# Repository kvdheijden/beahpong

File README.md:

# Beahpong
Linux (raspberry pi 4B+) kernel module + device tree for a Beahpong table

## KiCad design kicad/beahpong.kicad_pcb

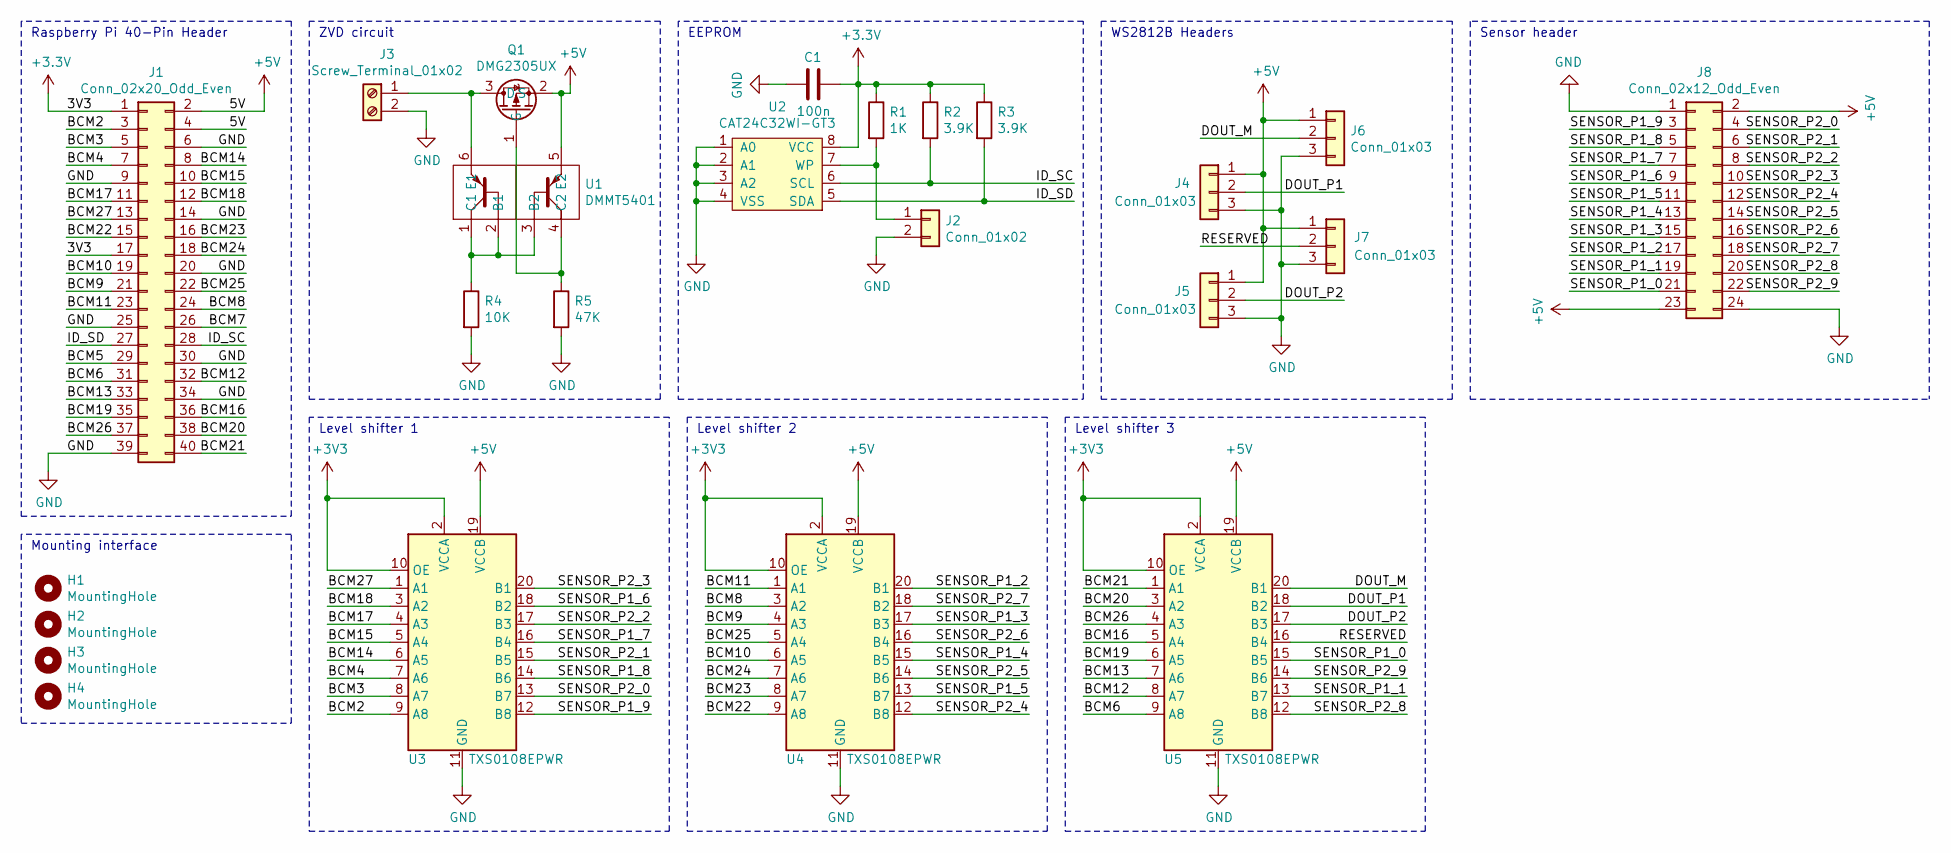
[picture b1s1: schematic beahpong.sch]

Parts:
C1: 100n; C_0402_1005Metric; LCSC C1525
H1, H2, H3, H4: MountingHole; MountingHole_2.75mm_M2.5_Land_6.2mm
J1: Conn_02x20_Odd_Even; PinSocket_2x20_P2.54mm_Vertical
J2: Conn_01x02; PinHeader_1x02_P2.54mm_Vertical
J3: Screw_Terminal_01x02; PhoenixContact_MC_1,5_2-G-3.5_1x02_P3.50mm_Horizontal
J4, J5, J6, J7: Conn_01x03; PinHeader_1x03_P2.54mm_Vertical
J8: Conn_02x12_Odd_Even; PinHeader_2x12_P2.54mm_Vertical
Q1: DMG2305UX; SOT-23; LCSC C144153
R1: 1K; R_0402_1005Metric; LCSC C11702
R2, R3: 3.9K; R_0402_1005Metric; LCSC C51721
R4: 10K; R_0402_1005Metric; LCSC C25744
R5: 47K; R_0402_1005Metric; LCSC C25792
U1: DMMT5401; SOT-23-6; LCSC C154733
U2: CAT24C32WI−GT3; SOIC-8_3.9x4.9mm_P1.27mm; LCSC C81193
U3, U4, U5: TXS0108EPWR; TSSOP-20_4.4x6.5mm_P0.65mm; LCSC C17206

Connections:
+5V: J1.2, J1.4, J4.1, J5.1, J6.1, J7.1, J8.2, J8.23, Q1.2 (S), U1.5 (E2), U3.19 (VCCB), U4.19 (VCCB), U5.19 (VCCB)
/BCM2: J1.3, U3.9 (A8)
/BCM3: J1.5, U3.8 (A7)
/BCM4: J1.7, U3.7 (A6)
/BCM6: J1.31, U5.9 (A8)
/BCM8: J1.24, U4.3 (A2)
/BCM9: J1.21, U4.4 (A3)
/BCM10: J1.19, U4.6 (A5)
/BCM11: J1.23, U4.1 (A1)
/BCM12: J1.32, U5.8 (A7)
/BCM13: J1.33, U5.7 (A6)
/BCM14: J1.8, U3.6 (A5)
/BCM15: J1.10, U3.5 (A4)
/BCM16: J1.36, U5.5 (A4)
/BCM17: J1.11, U3.4 (A3)
/BCM18: J1.12, U3.3 (A2)
/BCM19: J1.35, U5.6 (A5)
/BCM20: J1.38, U5.3 (A2)
/BCM21: J1.40, U5.1 (A1)
/BCM22: J1.15, U4.9 (A8)
/BCM23: J1.16, U4.8 (A7)
/BCM24: J1.18, U4.7 (A6)
/BCM25: J1.22, U4.5 (A4)
/BCM26: J1.37, U5.4 (A3)
/BCM27: J1.13, U3.1 (A1)
/DOUT_M: J6.2, U5.20 (B1)
/DOUT_P1: J4.2, U5.18 (B2)
/DOUT_P2: J5.2, U5.17 (B3)
/ID_SC: J1.28, R2.2, U2.6 (SCL)
/ID_SD: J1.27, R3.2, U2.5 (SDA)
/RESERVED: J7.2, U5.16 (B4)
/SENSOR_P1_0: J8.21, U5.15 (B5)
/SENSOR_P1_1: J8.19, U5.13 (B7)
/SENSOR_P1_2: J8.17, U4.20 (B1)
/SENSOR_P1_3: J8.15, U4.17 (B3)
/SENSOR_P1_4: J8.13, U4.15 (B5)
/SENSOR_P1_5: J8.11, U4.13 (B7)
/SENSOR_P1_6: J8.9, U3.18 (B2)
/SENSOR_P1_7: J8.7, U3.16 (B4)
/SENSOR_P1_8: J8.5, U3.14 (B6)
/SENSOR_P1_9: J8.3, U3.12 (B8)
/SENSOR_P2_0: J8.4, U3.13 (B7)
/SENSOR_P2_1: J8.6, U3.15 (B5)
/SENSOR_P2_2: J8.8, U3.17 (B3)
/SENSOR_P2_3: J8.10, U3.20 (B1)
/SENSOR_P2_4: J8.12, U4.12 (B8)
/SENSOR_P2_5: J8.14, U4.14 (B6)
/SENSOR_P2_6: J8.16, U4.16 (B4)
/SENSOR_P2_7: J8.18, U4.18 (B2)
/SENSOR_P2_8: J8.20, U5.12 (B8)
/SENSOR_P2_9: J8.22, U5.14 (B6)
GND: C1.1, J1.6, J1.9, J1.14, J1.20, J1.25, J1.30, J1.34, J1.39, J2.2, J3.2, J4.3, J5.3, J6.3, J7.3, J8.1, J8.24, R4.2, R5.2, U2.1 (A0), U2.2 (A1), U2.3 (A2), U2.4 (VSS), U3.11 (GND), U4.11 (GND), U5.11 (GND)
unnamed: J2.1, R1.2, U2.7 (WP)
unnamed: J3.1, Q1.3 (D), U1.6 (E1)
unnamed: Q1.1 (G), R5.1, U1.4 (C2)
unnamed: R4.1, U1.1 (C1), U1.2 (B1), U1.3 (B2)

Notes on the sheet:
Raspberry Pi 40-Pin Header
ZVD circuit
EEPROM
Mounting interface
Level shifter 2
Level shifter 1
Level shifter 3
WS2812B Headers
Sensor header

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
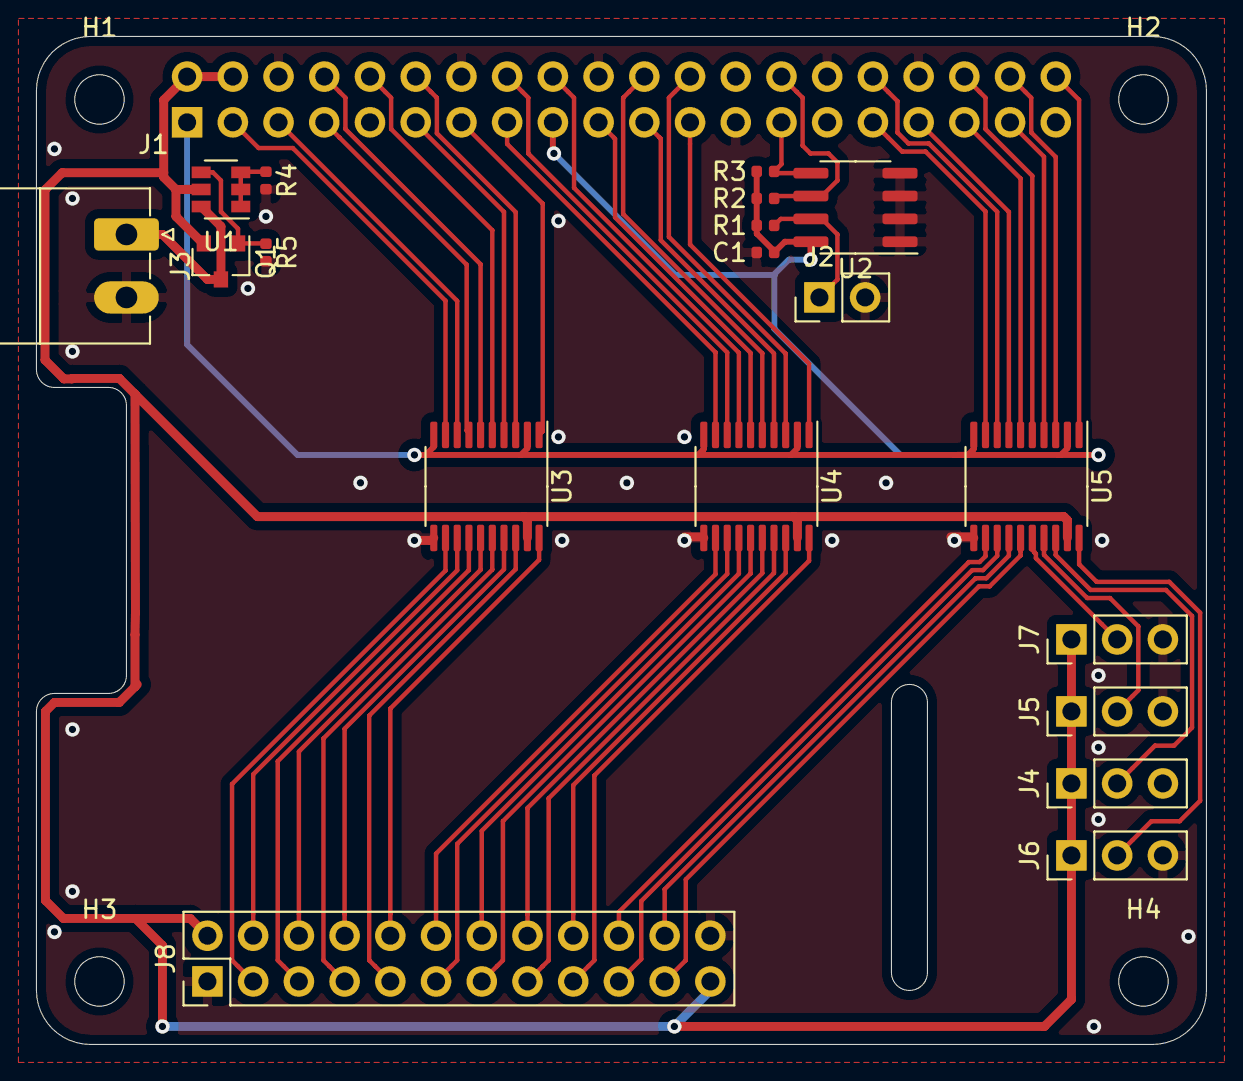
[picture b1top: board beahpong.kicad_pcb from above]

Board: 2 copper layers, 65.0 x 56.0 mm, 24 parts (1 on the bottom side), 57 nets.

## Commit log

2020-05-23 Update dts
2020-05-24 Add ui project
2020-05-24 Cmakify
2020-06-17 Add RPI hat KiCad project
2020-06-18 Add level shifters
2020-07-02 Finished layout of pcb
2020-07-03 Change level shifter to one from LCSC database
